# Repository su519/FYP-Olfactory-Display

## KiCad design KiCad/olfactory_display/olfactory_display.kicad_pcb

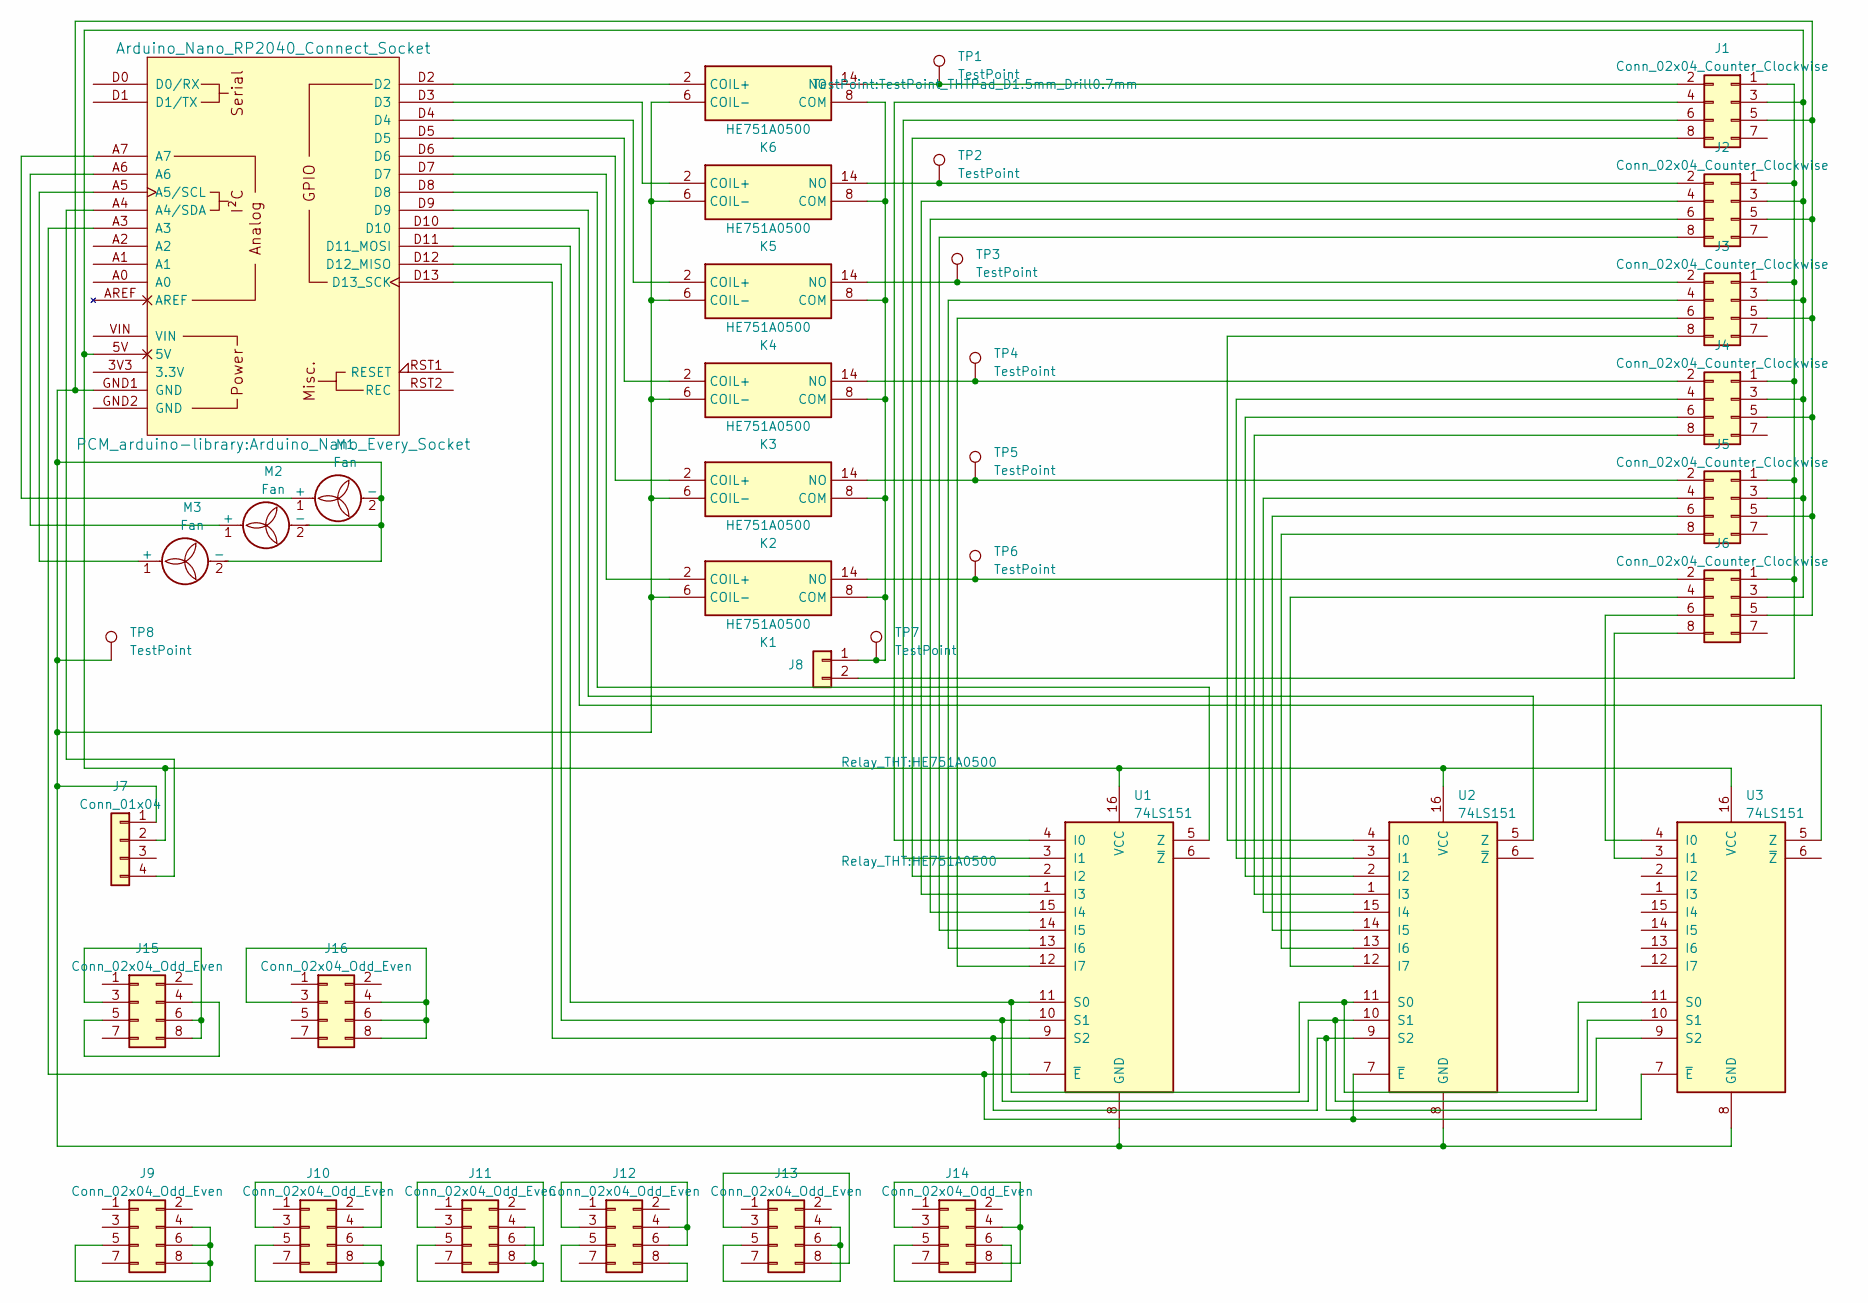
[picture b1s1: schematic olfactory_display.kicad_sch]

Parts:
J1, J2, J3, J4, J5, J6: Conn_02x04_Counter_Clockwise; PinSocket_2x04_P2.54mm_Vertical
J7: Conn_01x04; PinHeader_1x04_P2.00mm_Vertical
J8: Conn_01x02; PinHeader_1x02_P2.00mm_Vertical
J9, J10, J11, J12, J13, J14, J15, J16: Conn_02x04_Odd_Even; PinHeader_2x04_P2.54mm_Vertical
K1, K2, K3, K4, K5, K6: HE751A0500; Manufacturer_Part_Number HE751A0500; Mouser Part Number 934-HE751A0500
M1, M2, M3: Fan; PinHeader_1x02_P2.00mm_Vertical
TP1, TP2, TP3, TP4, TP5, TP6, TP7, TP8: TestPoint; TestPoint_THTPad_D1.5mm_Drill0.7mm
U1, U2, U3: 74LS151; DIP-16_W10.16mm
XA1: Arduino_Nano_RP2040_Connect_Socket; Arduino_Nano_Every_Socket

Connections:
unnamed: J1.1, J2.1, J3.1, J4.1, J5.1, J6.1, J8.2
unnamed: J1.2, K6.14 (NO), TP1.1
unnamed: J1.3, J2.3, J3.3, J4.3, J5.3, J6.3, J7.2, U1.16 (VCC), U2.16 (VCC), U3.16 (VCC), XA1.5V
unnamed: J1.4, U1.4 (I0)
unnamed: J1.5, J2.5, J3.5, J4.5, J5.5, J6.5, J7.1, K1.6 (COIL-), K2.6 (COIL-), K3.6 (COIL-), K4.6 (COIL-), K5.6 (COIL-), K6.6 (COIL-), M1.2 (-), M2.2 (-), M3.2 (-), TP8.1, U1.8 (GND), U2.8 (GND), U3.8 (GND), XA1.GND1 (GND)
unnamed: J1.6, U1.3 (I1)
unnamed: J1.8, U1.2 (I2)
unnamed: J2.2, K5.14 (NO), TP2.1
unnamed: J2.4, U1.1 (I3)
unnamed: J2.6, U1.15 (I4)
unnamed: J2.8, U1.14 (I5)
unnamed: J3.2, K4.14 (NO), TP3.1
unnamed: J3.4, U1.13 (I6)
unnamed: J3.6, U1.12 (I7)
unnamed: J3.8, U2.4 (I0)
unnamed: J4.2, K3.14 (NO), TP4.1
unnamed: J4.4, U2.3 (I1)
unnamed: J4.6, U2.2 (I2)
unnamed: J4.8, U2.1 (I3)
unnamed: J5.2, K2.14 (NO), TP5.1
unnamed: J5.4, U2.15 (I4)
unnamed: J5.6, U2.14 (I5)
unnamed: J5.8, U2.13 (I6)
unnamed: J6.2, K1.14 (NO), TP6.1
unnamed: J6.4, U2.12 (I7)
unnamed: J6.6, U3.4 (I0)
unnamed: J6.8, U3.3 (I1)
unnamed: J7.4, XA1.A4 (A4/SDA)
unnamed: J8.1, K1.8 (COM), K2.8 (COM), K3.8 (COM), K4.8 (COM), K5.8 (COM), K6.8 (COM), TP7.1
unnamed: J9.4, J9.5, J9.6, J9.8
unnamed: J10.3, J10.4
unnamed: J10.5, J10.6, J10.8
unnamed: J11.3, J11.6
unnamed: J11.4, J11.5, J11.8
unnamed: J12.3, J12.4, J12.6
unnamed: J12.5, J12.8
unnamed: J13.3, J13.8
unnamed: J13.4, J13.5, J13.6
unnamed: J14.3, J14.4, J14.8
unnamed: J14.5, J14.6
unnamed: J15.3, J15.6, J15.8
unnamed: J15.4, J15.5
unnamed: J16.3, J16.4, J16.6, J16.8
unnamed: K1.2 (COIL+), XA1.D7
unnamed: K2.2 (COIL+), XA1.D6
unnamed: K3.2 (COIL+), XA1.D5
unnamed: K4.2 (COIL+), XA1.D4
unnamed: K5.2 (COIL+), XA1.D3
unnamed: K6.2 (COIL+), XA1.D2
unnamed: M1.1 (+), XA1.A7
unnamed: M2.1 (+), XA1.A6
unnamed: M3.1 (+), XA1.A5 (A5/SCL)
unnamed: U1.11 (S0), U2.11 (S0), U3.11 (S0), XA1.D11 (D11_MOSI)
unnamed: U1.10 (S1), U2.10 (S1), U3.10 (S1), XA1.D12 (D12_MISO)
unnamed: U1.9 (S2), U2.9 (S2), U3.9 (S2), XA1.D13 (D13_SCK)
unnamed: U1.5 (Z), XA1.D8
unnamed: U1.7 (~E), U2.7 (~E), U3.7 (~E), XA1.A3
unnamed: U2.5 (Z), XA1.D9
unnamed: U3.5 (Z), XA1.D10

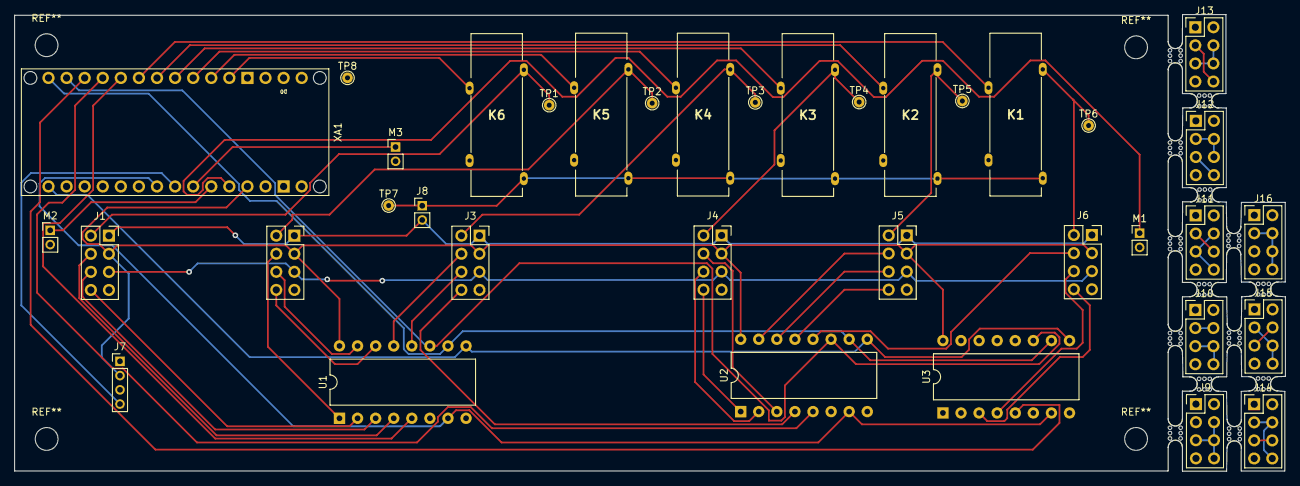
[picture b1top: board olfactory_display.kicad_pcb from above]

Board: 2 copper layers, 178.5 x 64.1 mm, 51 parts (0 on the bottom side), 59 nets.

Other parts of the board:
mouse-bite-2mm-slot, mouse-bite-2mm-slot#2, mouse-bite-2mm-slot#3, mouse-bite-2mm-slot#4, mouse-bite-2mm-slot#5, mouse-bite-2mm-slot#6, mouse-bite-2mm-slot#7, mouse-bite-2mm-slot#8, mouse-bite-2mm-slot#9, mouse-bite-2mm-slot#10, mouse-bite-2mm-slot#11, mouse-bite-2mm-slot#12, mouse-bite-2mm-slot#13, mouse-bite-2mm-slot#14: VAL**; mouse-bite-2mm-slot

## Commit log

2023-05-14 3D models and Arduino wifi code
2023-05-14 Unity start screen
2023-05-17 Configure Git LFS for large files
2023-05-17 Configure Git LFS for Unix executable files
2023-05-17 Add .gitignore file to exclude Library/ and ArtifactDB
2023-05-17 Add .gitignore file to exclude ArtifactDB
2023-05-17 unity
2023-05-17 gitignore artifactdb
2023-05-19 cad redesign housing and atomizer holder
2023-05-19 arduino tests
2023-05-19 Multiplexer binary read
2023-05-19 multiplexer binary code implementation unity and arduino
2023-05-19 pwm function fixed - arduino
2023-05-20 PWM moved to Unity and made coroutine
2023-05-21 User study panel and user study 1 button mapping
2023-05-21 Added white noise
2023-05-21 Back buttons
2023-05-21 Double digit pins implemented
2023-05-22 user study 1 code complete
2023-05-22 random index
2023-05-30 atomizer redesign and user test
2023-06-03 intensity controller
2023-06-04 KiCad files
2023-06-07 user test 2 code
2023-06-07 Create e398c5150c4ffefa223cc9bdda247833
2023-06-10 Interest gration
2023-06-11 user test 4 and casing cover
2023-06-17 Testing
2023-06-19 photos
2023-06-21 analysis
2023-06-21 final
2023-06-21 arduino
